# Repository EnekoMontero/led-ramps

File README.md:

# led-ramps
Simple board so you can add rgb leds to your 3D printer easily

Nota: El circuito está pensado para una única capa de tal forma de que se pueda hacer de forma simple usando una cnc.
En concreto he usado una Cyclone PCB Factory.

Tutorial: http://haudahau.com/vadedos/?p=1226

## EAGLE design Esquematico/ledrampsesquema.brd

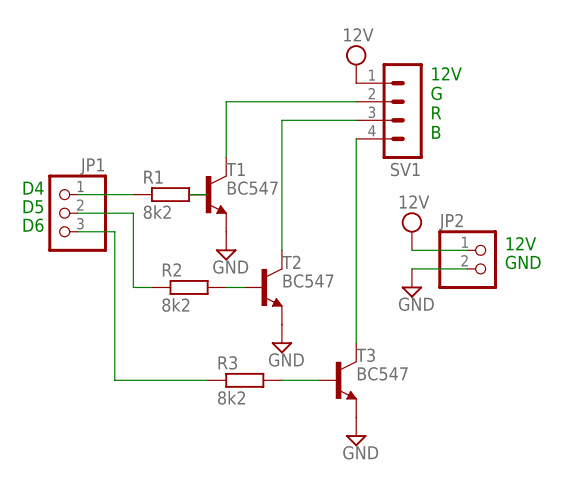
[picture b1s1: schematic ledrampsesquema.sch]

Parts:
JP1: PINHD-1X3; 1X03
JP2: PINHD-1X2; 1X02
R1, R2, R3: 8k2; 0204/7
SV1: MA04-1
T1, T2, T3: BC547; TO92

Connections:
GND: JP2.2, T1.1 (E), T2.1 (E), T3.1 (E)
unnamed: R1.2, T1.2 (B)
unnamed: JP1.1, R1.1
unnamed: SV1.2, T1.3 (C)
unnamed: SV1.3, T2.3 (C)
unnamed: SV1.4, T3.3 (C)
unnamed: R2.2, T2.2 (B)
unnamed: R3.2, T3.2 (B)
unnamed: JP1.2, R2.1
unnamed: JP1.3, R3.1
VCC: JP2.1, SV1.1

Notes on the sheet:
12V G R B
12V
GND

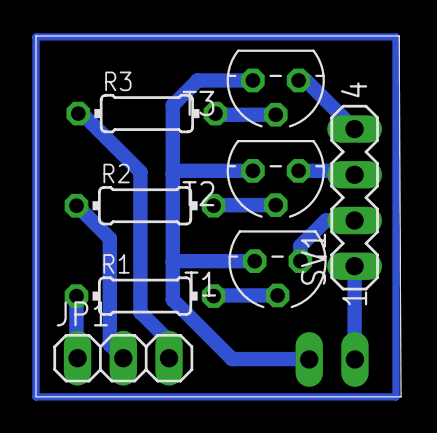
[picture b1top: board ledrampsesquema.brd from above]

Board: 2 copper layers, 20.3 x 20.1 mm, 9 parts (1 on the bottom side), 11 nets.

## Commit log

2016-10-09 Added files
    Added board, schematic, gerbers and some photos.
2016-10-12 Añadidos ficheros para imprimir carcasa y reorganización de los ficheros
